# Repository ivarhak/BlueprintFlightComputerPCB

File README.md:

Files for my flight computer project as a part of the Hack Club foundation's Blueprint program 2025.
Board has an STM chip, 2 BMP351 barometers, 1 ICM-42688-P IMU, a microSD slot, battery charging capabilities, and servo pins.
Feel free to use and modify.

The main idea with the board is to have a solid platform on which there are high-quality sensors to put on any rocketry project. The two barometers help eliminate noise, and the ICM is of high quality. The two servo pin headers let the user connect this flight computer to any PWM project, like airbrakes or canard systems. 

Special thanks to @Notaroomba, Hack Club, and @rasmushauschild for creating the guides and tools necessary to make this awesome PCB.
3d model can be found in the hardware folder, was so big I had to compress it.

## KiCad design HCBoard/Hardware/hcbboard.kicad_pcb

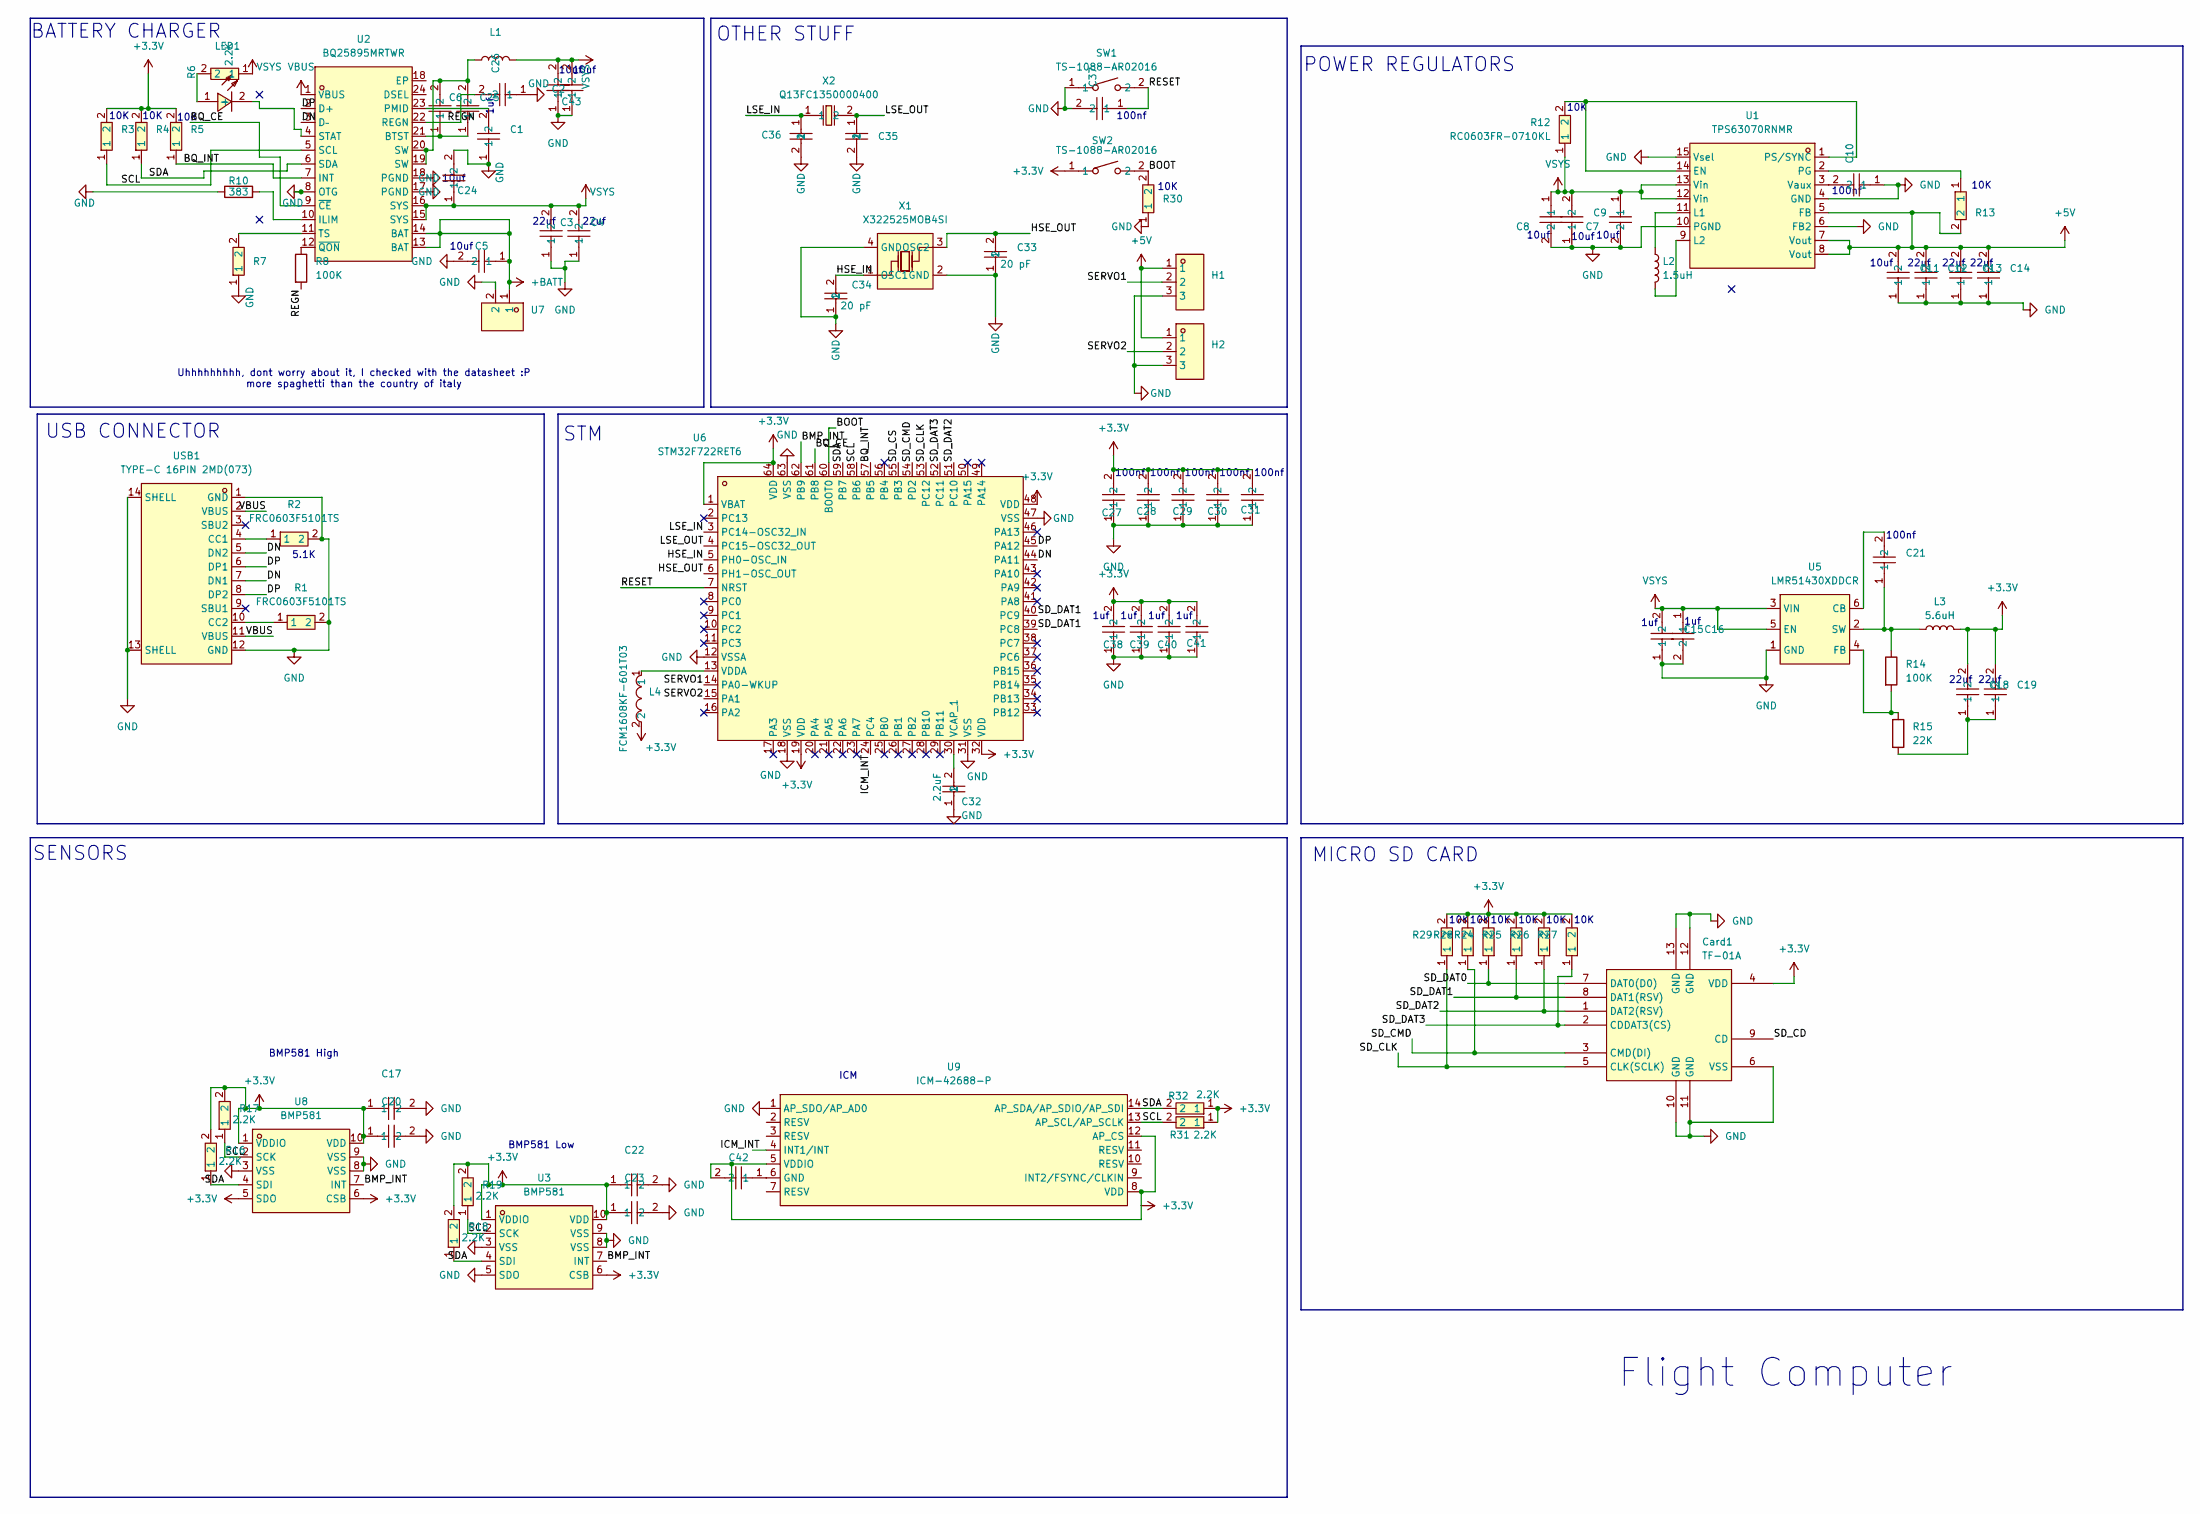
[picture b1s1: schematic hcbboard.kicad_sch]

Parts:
C1, C2, C5, C7, C8, C9, C11, C24, C43: CL21A106KAYNNNE; C0805; LCSC Part C15850
C3, C4, C6, C12, C13, C14, C25: CL21A226MAYNNNE; C0805; LCSC Part C602037
C10, C17, C20, C21, C22, C23, C27, C28, C29, C30, C31, C37, C42: CL10A105KB8NNNC; C_0201_0603Metric; LCSC Part C14663
C15, C16, C26, C38, C39, C40, C41: CL10A105KB8NNNC; C_0201_0603Metric; LCSC Part C15849
C18, C19: CL21A226MAYNNNE; C_0805_2012Metric; LCSC Part C602037
C32: CL10A225KO8NNNC; C0603; LCSC Part C23630
C33, C34: CL10C200JB8NNNC; C0603; LCSC Part C1648
C35, C36: 0603CG6R8C500NT; C0603; LCSC Part C1679
Card1: TF-01A; TF-SMD_TF-01A; LCSC Part C91145
H1, H2: HX PH254-01-03-Z-L11.5 PCB PIN HEADER; HDR-TH_3P-P2.54-V-M-1; LCSC Part C52016391
L1, L2: 1.5uH; L_1008_2520Metric
L3: 5.6uH; L_Changjiang_FXL0630
L4: FCM1608KF-601T03; L0603; LCSC Part C141723
LED1: YLED0603R; LED0603-FD; LCSC Part C19171390
R1, R2: FRC0603F5101TS; R0603; LCSC Part C2907044
R3, R4, R5, R7, R12, R13, R24, R25, R26, R27, R28, R29, R30: RC0603FR-0710KL; R0603; LCSC Part C98220
R6, R16, R17, R18, R19, R31, R32: 0805W8F2201T5E; R0805; LCSC Part C17520
R8, R14: 100K; R_0201_0603Metric
R10: 383; C_0402_1005Metric
R15: 22K; R_0201_0603Metric
SW1, SW2: TS-1088-AR02016; SW-SMD_L3.9-W3.0-P4.45; LCSC Part C720477
U1: TPS63070RNMR; VQFN-HR-15_L3.0-W2.5-P0.50-BL_TPS63070RNMR; LCSC Part C109322
U2: BQ25895MRTWR; WQFN-24_L4.0-W4.0-P0.50-TL-EP2.7; LCSC Part C485917
U3, U8: BMP581; LGA-10_L2.0-W2.0-P0.50-TL_BMP581; LCSC Part C5362283
U5: LMR51430XDDCR; SOT-23-6_L2.9-W1.6-P0.95-LS2.8-BL; LCSC Part C5185863
U6: STM32F722RET6; LQFP-64_L10.0-W10.0-P0.50-LS12.0-BL; LCSC Part C118207
U7: DB301V-3.5-2P-GN; CONN-TH_DB301V-3.5-2P-GN; LCSC Part C695629
U9: ICM-42688-P; LGA-14_L3.0-W2.5-P0.50-TL; LCSC Part C1850418
USB1: TYPE-C 16PIN 2MD(073); USB-C-SMD_TYPE-C-6PIN-2MD-073; LCSC Part C2765186
X1: X322525MOB4SI; CRYSTAL-SMD_4P-L3.2-W2.5-BL; LCSC Part C9006
X2: Q13FC1350000400; FC-135R_L3.2-W1.5; LCSC Part C32346

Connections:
+3.3V: C17.1, C18.2, C19.2, C20.1, C22.1, C23.1, C27.2, C28.2, C29.2, C30.2, C31.2, C38.2, C39.2, C40.2, C41.2, Card1.4 (VDD), L3.2, L4.2, R3.2, R4.2, R5.2, R16.2, R17.2, R18.2, R19.2, R24.2, R25.2, R26.2, R27.2, R28.2, R29.2, R31.1, R32.1, SW2.1, U3.1 (VDDIO), U3.6 (CSB), U3.10 (VDD), U6.1 (VBAT), U6.19 (VDD), U6.32 (VDD), U6.48 (VDD), U6.64 (VDD), U8.1 (VDDIO), U8.5 (SDO), U8.6 (CSB), U8.10 (VDD)
+5V: C11.2, C12.2, C13.2, C14.2, H1.1, H2.1, R13.2, U1.5 (FB), U1.7 (Vout), U1.8 (Vout)
+BATT: C5.1, U2.13 (BAT), U2.14 (BAT), U7.1
/BMP_INT: U3.7 (INT), U6.62 (PB9), U8.7 (INT)
/BOOT: R30.2, SW2.2, U6.60 (BOOT0)
/BQ_CE: U2.9 (~CE), U6.61 (PB8)
/BQ_INT: R5.1, U2.7 (INT), U6.57 (PB5)
/DP: U2.2 (D+), U6.45 (PA12), USB1.6 (DP1), USB1.8 (DP2)
/HSE_IN: C34.2, U6.5 (PH0-OSC_IN), X1.1 (OSC1)
/HSE_OUT: C33.2, U6.6 (PH1-OSC_OUT), X1.3 (OSC2)
/ICM_INT: U6.24 (PC4), U9.4 (INT1/INT)
/LSE_IN: C36.1, U6.3 (PC14-OSC32_IN), X2.1
/LSE_OUT: C35.1, U6.4 (PC15-OSC32_OUT), X2.2
/REGN: C26.2, R8.2, U2.22 (REGN)
/RESET: C37.1, SW1.2, U6.7 (NRST)
/SCL: R3.1, R17.1, R19.1, R31.2, U2.5 (SCL), U3.2 (SCK), U6.58 (PB6), U8.2 (SCK), U9.13 (AP_SCL/AP_SCLK)
/SDA: R4.1, R16.1, R18.1, R32.2, U2.6 (SDA), U3.4 (SDI), U6.59 (PB7), U8.4 (SDI), U9.14 (AP_SDA/AP_SDIO/AP_SDI)
/SD_CD: Card1.9 (CD)
/SD_CLK: Card1.5 (CLK(SCLK)), R29.1, U6.53 (PC12)
/SD_CMD: Card1.3 (CMD(DI)), R28.1, U6.54 (PD2)
/SD_CS: U6.55 (PB3)
/SD_DAT0: Card1.7 (DAT0(D0)), R24.1
/SD_DAT1: Card1.8 (DAT1(RSV)), R25.1, U6.39 (PC8), U6.40 (PC9)
/SD_DAT2: Card1.1 (DAT2(RSV)), R26.1, U6.51 (PC10)
/SD_DAT3: Card1.2 (CDDAT3(CS)), R27.1, U6.52 (PC11)
/SERVO1: H1.2, U6.14 (PA0-WKUP)
/SERVO2: H2.2, U6.15 (PA1)
GND: C1.1, C2.1, C3.1, C4.1, C5.2, C7.2, C8.2, C9.1, C10.1, C11.1, C12.1, C13.1, C14.1, C15.1, C16.2, C17.2, C20.2, C22.2, C23.2, C24.2, C26.1, C27.1, C28.1, C29.1, C30.1, C31.1, C32.1, C33.1, C34.1, C35.2, C36.2, C37.2, C38.1, C39.1, C40.1, C41.1, C43.1, Card1.6 (VSS), Card1.10 (GND), Card1.11 (GND), Card1.12 (GND), Card1.13 (GND), H1.3, H2.3, R1.2, R2.2, R7.1, R10.1, R30.1, SW1.1, U1.4 (GND), U1.6 (FB2), U1.10 (PGND), U1.15 (Vsel), U2.8 (OTG), U2.17 (PGND), U2.18 (PGND), U3.3 (VSS), U3.5 (SDO), U3.8 (VSS), U3.9 (VSS), U5.1 (GND), U6.12 (VSSA), U6.18 (VSS), U6.31 (VSS), U6.47 (VSS), U6.63 (VSS), U7.2, U8.3 (VSS), U8.8 (VSS), U8.9 (VSS), U9.1 (AP_SDO/AP_AD0), USB1.1 (GND), USB1.12 (GND), USB1.13 (SHELL), USB1.14 (SHELL), X1.2 (GND), X1.4 (GND)
unnamed: C18.1, C19.1, R15.2
unnamed: C6.2, C25.2, L1.1, U2.19 (SW), U2.20 (SW)
unnamed: LED1.1 (+), R6.2
unnamed: LED1.2 (-), U2.4 (STAT)
unnamed: R12.2, U1.1 (PS/SYNC), U1.14 (EN)
unnamed: L2.1, U1.11 (L1)
unnamed: L2.2, U1.9 (L2)
unnamed: R13.1, U1.2 (PG)
unnamed: C10.2, U1.3 (Vaux)
unnamed: C6.1, C25.1, U2.21 (BTST)
unnamed: R10.2, U2.10 (ILIM)
unnamed: C1.2, U2.23 (PMID)
unnamed: R7.2, U2.11 (TS)
unnamed: R8.1, U2.12 (~QON)
unnamed: C21.2, U5.6 (CB)
unnamed: R14.2, R15.1, U5.4 (FB)
unnamed: C21.1, L3.1, R14.1, U5.2 (SW)
unnamed: C32.2, U6.30 (VCAP_1)
unnamed: L4.1, U6.13 (VDDA)
unnamed: C42.2, U9.5 (VDDIO), U9.8 (VDD), U9.12 (AP_CS)
unnamed: C42.1, U9.6 (GND)
unnamed: R2.1, USB1.4 (CC1)
unnamed: R1.1, USB1.10 (CC2)
VSYS: C2.2, C3.2, C4.2, C7.1, C8.1, C9.2, C15.2, C16.1, C24.1, C43.2, L1.2, R6.1, R12.1, U1.12 (Vin), U1.13 (Vin), U2.15 (SYS), U2.16 (SYS), U5.3 (VIN), U5.5 (EN)

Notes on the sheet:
1uf
22uf
10uf
10K
5.1K
POWER REGULATORS
100nf
BATTERY CHARGER
ICM
USB CONNECTOR
STM
OTHER STUFF
SENSORS
MICRO SD CARD
BMP581 Low
Uhhhhhhhhh, dont worry about it, I checked with the datasheet :P more spaghetti than the country of italy
Flight Computer
BMP581 High

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
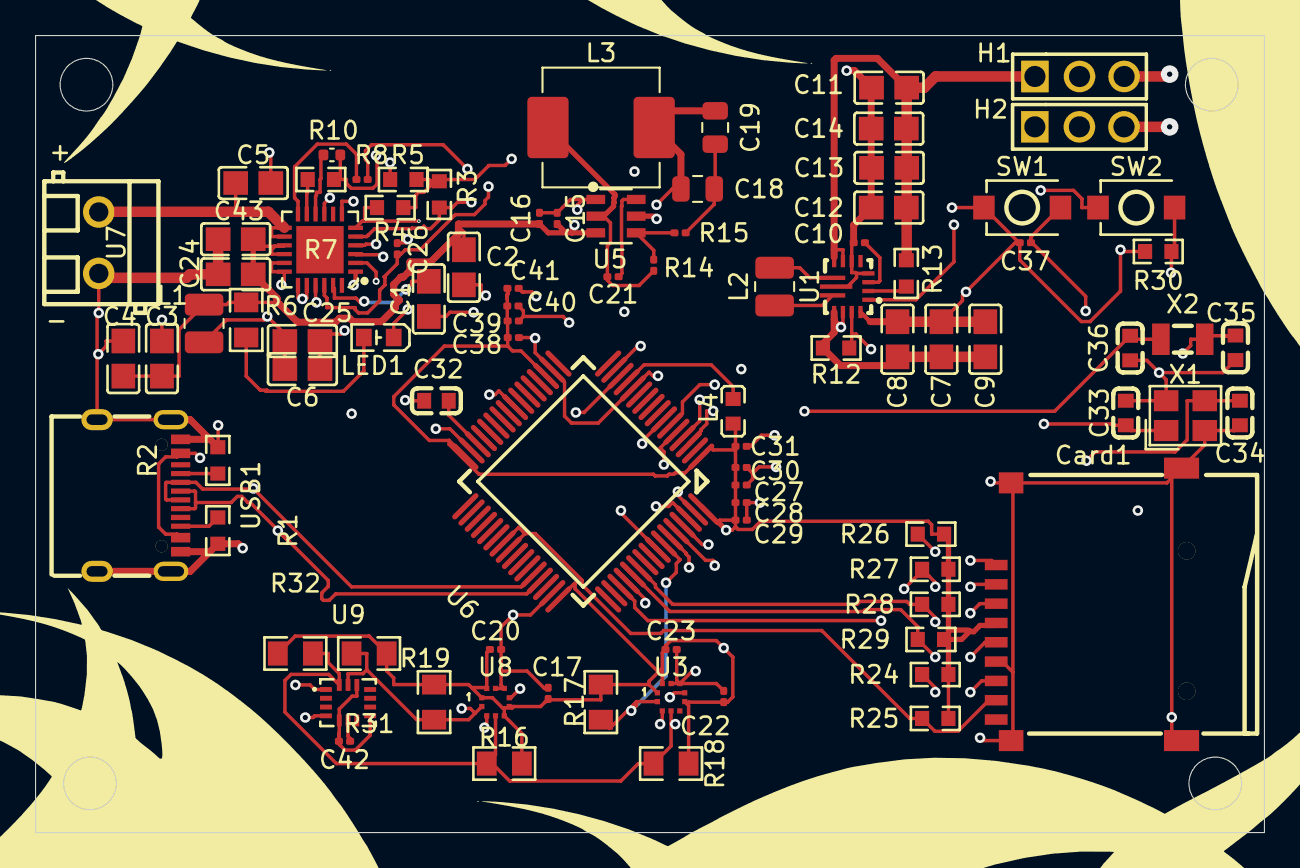
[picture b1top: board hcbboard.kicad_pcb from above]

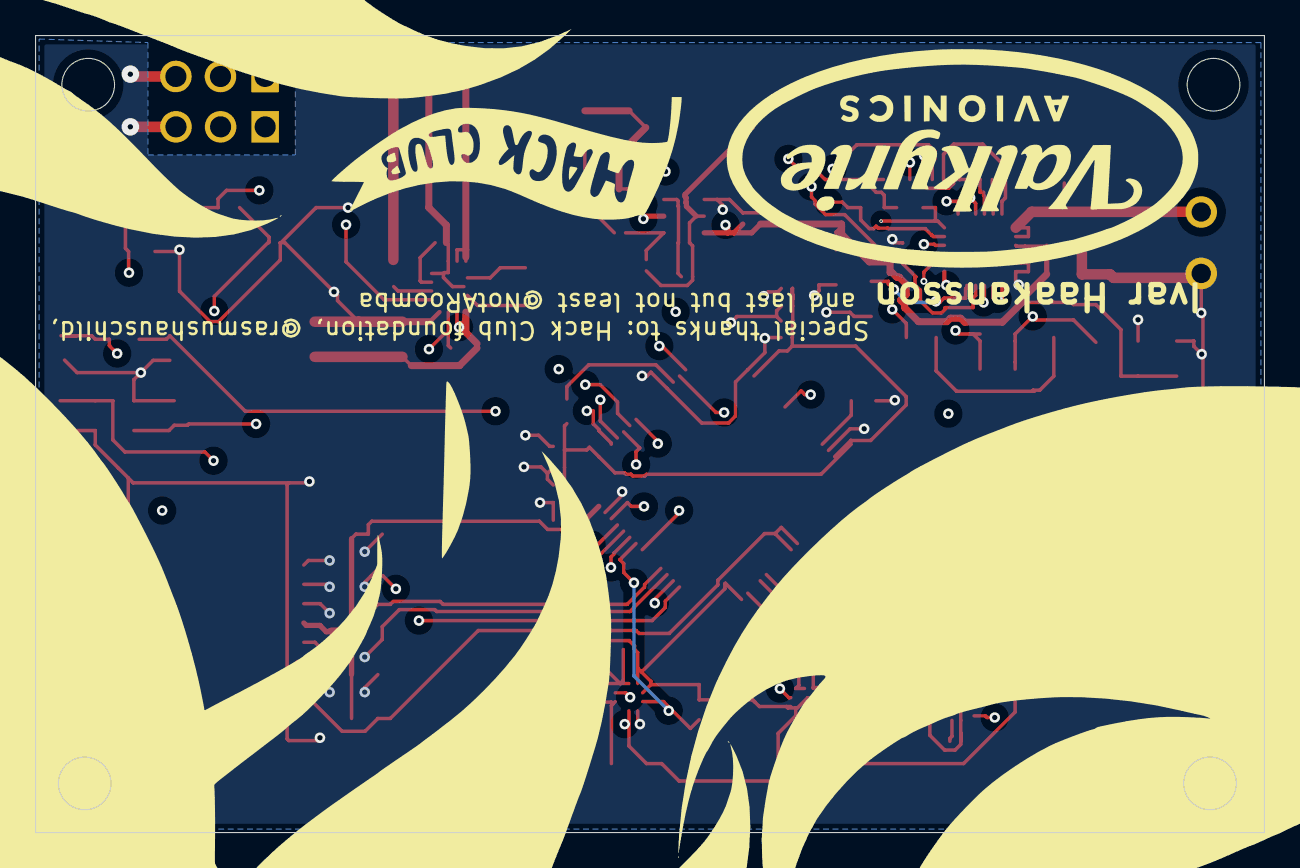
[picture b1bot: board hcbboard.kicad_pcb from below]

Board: 4 copper layers, 70.0 x 45.4 mm, 106 parts (7 on the bottom side), 52 nets.

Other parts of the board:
6765765: LOGO
G1313, G12414, G42414, G54353, G67567, G112323, G0202002, G321213, G424124, G546546, G567567, G756657, G757657, G2423423, G45345435: LOGO

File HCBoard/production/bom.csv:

Designator,Footprint,Quantity,Value,LCSC Part #
"C1, C11, C2, C24, C43, C5, C7, C8, C9",C0805,9,CL21A106KAYNNNE,C15850
"C10, C17, C20, C21, C22, C23, C27, C28, C29, C30, C31, C37, C42",0201,13,CL10A105KB8NNNC,C14663
"C12, C13, C14, C25, C3, C4, C6",C0805,7,CL21A226MAYNNNE,C602037
"C15, C16, C26, C38, C39, C40, C41",0201,7,CL10A105KB8NNNC,C15849
"C18, C19",0805,2,CL21A226MAYNNNE,C602037
C32,C0603,1,CL10A225KO8NNNC,C23630
"C33, C34",C0603,2,CL10C200JB8NNNC,C1648
"C35, C36",C0603,2,0603CG6R8C500NT,C1679
CARD1,TF-SMD_TF-01A,1,TF-01A,C91145
"H1, H2",HDR-TH_3P-P2.54-V-M-1,2,HX PH254-01-03-Z-L11.5 PCB PIN HEADER,C52016391
"L1, L2",1008,2,1.5uH,
L3,L_Changjiang_FXL0630,1,5.6uH,
L4,L0603,1,FCM1608KF-601T03,C141723
LED1,LED0603-FD,1,YLED0603R,C19171390
"R1, R2",R0603,2,FRC0603F5101TS,C2907044
R10,0402,1,383,
"R12, R13, R24, R25, R26, R27, R28, R29, R3, R30, R4, R5, R7",R0603,13,RC0603FR-0710KL,C98220
"R14, R8",0201,2,100K,
R15,0201,1,22K,
"R16, R17, R18, R19, R31, R32, R6",R0805,7,0805W8F2201T5E,C17520
"SW1, SW2",SW-SMD_L3.9-W3.0-P4.45,2,TS-1088-AR02016,C720477
U1,VQFN-HR-15_L3.0-W2.5-P0.50-BL_TPS63070RNMR,1,TPS63070RNMR,C109322
U2,WQFN-24_L4.0-W4.0-P0.50-TL-EP2.7,1,BQ25895MRTWR,C485917
"U3, U8",LGA-10_L2.0-W2.0-P0.50-TL_BMP581,2,BMP581,C5362283
U5,SOT-23-6_L2.9-W1.6-P0.95-LS2.8-BL,1,LMR51430XDDCR,C5185863
U6,LQFP-64_L10.0-W10.0-P0.50-LS12.0-BL,1,STM32F722RET6,C118207
U7,CONN-TH_DB301V-3.5-2P-GN,1,DB301V-3.5-2P-GN,C695629
U9,LGA-14_L3.0-W2.5-P0.50-TL,1,ICM-42688-P,C1850418
USB1,USB-C-SMD_TYPE-C-6PIN-2MD-073,1,TYPE-C 16PIN 2MD(073),C2765186
X1,CRYSTAL-SMD_4P-L3.2-W2.5-BL,1,X322525MOB4SI,C9006
X2,FC-135R_L3.2-W1.5,1,Q13FC1350000400,C32346

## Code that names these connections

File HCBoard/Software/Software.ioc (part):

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Mcu.Name=STM32F722R(C-E)Tx
Mcu.Package=LQFP64
Mcu.UserName=STM32F722RETx
PA0-WKUP.Signal=S_TIM2_CH1_ETR
PA1.Signal=S_TIM2_CH2
PA11.Mode=Host_Only
PA11.Signal=USB_OTG_FS_DM
PA12.Mode=Host_Only
PA12.Signal=USB_OTG_FS_DP
PA4.Mode=NSS_Signal_Hard_Output
PA4.Signal=SPI1_NSS
PA5.Mode=Full_Duplex_Master
PA5.Signal=SPI1_SCK
PA6.Mode=Full_Duplex_Master
PA6.Signal=SPI1_MISO
PA7.Mode=Full_Duplex_Master
PA7.Signal=SPI1_MOSI
PB3.GPIOParameters=GPIO_Label
PB3.GPIO_Label=SD_CS
PB3.Signal=GPIO_Input
PB5.GPIOParameters=GPIO_Label
PB5.GPIO_Label=BQ_INT
PB5.Signal=GPXTI5
PB6.Mode=I2C
PB6.Signal=I2C1_SCL
PB7.Mode=I2C
PB7.Signal=I2C1_SDA
PB8.GPIOParameters=GPIO_Label
PB8.GPIO_Label=BQ_CE
PB8.Signal=GPIO_Output
PB9.GPIOParameters=GPIO_Label
PB9.GPIO_Label=BMP_INT
PB9.Signal=GPXTI9
PC10.Mode=SD_4_bits_Wide_bus
PC10.Signal=SDMMC1_D2
PC11.Mode=SD_4_bits_Wide_bus
PC11.Signal=SDMMC1_D3
PC12.Mode=SD_4_bits_Wide_bus
PC12.Signal=SDMMC1_CK
PC14-OSC32_IN.Mode=LSE-External-Oscillator
PC14-OSC32_IN.Signal=RCC_OSC32_IN
PC15-OSC32_OUT.Mode=LSE-External-Oscillator
PC15-OSC32_OUT.Signal=RCC_OSC32_OUT
PC4.GPIOParameters=GPIO_Label
PC4.GPIO_Label=ICM_INT1
PC4.Signal=GPXTI4
PC8.Mode=SD_4_bits_Wide_bus
PC8.Signal=SDMMC1_D0
PC9.Mode=SD_4_bits_Wide_bus
PC9.Signal=SDMMC1_D1
PD2.Mode=SD_4_bits_Wide_bus
PD2.Signal=SDMMC1_CMD
PH0-OSC_IN.Mode=HSE-External-Oscillator
PH0-OSC_IN.Signal=RCC_OSC_IN
PH1-OSC_OUT.Mode=HSE-External-Oscillator
PH1-OSC_OUT.Signal=RCC_OSC_OUT
RCC.HSE_VALUE=25000000
board=custom

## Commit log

2025-12-07 Create hello
2025-12-07 Revise README with updated sensor and project details
    Updated sensor information and added details about the board's capabilities and resources.
